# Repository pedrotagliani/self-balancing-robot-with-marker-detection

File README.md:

<h1 align="center">Robot balanceador con detección de marcadores ArUco</h1>

<p>
En este proyecto, se diseñó y construyó un robot balanceador con dos funcionalidades principales. En primer lugar, se implementó un sistema de control remoto mediante una aplicación móvil, que permite mover el robot libremente en cualquier dirección. En segundo lugar, se desarrolló un sistema de equilibrio dinámico que utiliza una cámara para detectar marcadores ArUco y avanzar automáticamente cuando identifica uno en la imagen capturada.

El sistema de control de balance se basó en un controlador PID, ajustado para mantener al robot erguido en todo momento. Para medir el ángulo de inclinación, se utilizó un sensor MPU6050, que combina acelerómetro y giroscopio. Los datos obtenidos por este sensor fueron procesados en un Arduino Nano, que calculaba las señales de control necesarias para los motores. Además, se diseñaron y fabricaron placas PCB personalizadas para integrar los componentes eléctricos del sistema de manera eficiente.

El robot utilizó dos motores paso a paso NEMA 17, seleccionados por su precisión y torque, junto con controladores Pololu A4988 que gestionaron la dirección y velocidad de los motores. Para la comunicación remota, se incorporó un módulo Bluetooth HC-05, que permitió manejar el robot desde una aplicación móvil con una interfaz tipo joystick, facilitada por la biblioteca BalancingWii. Este sistema proporcionó un control intuitivo y responsivo del robot mediante una conexión estable y confiable.

El equilibrio dinámico se logró gracias al controlador PID, que ajustaba de manera constante la velocidad de los motores en función de la inclinación detectada por el sensor. Este algoritmo permitió que el robot se adaptara rápidamente a cambios en el terreno o a variaciones en su carga, manteniéndose estable en diversas condiciones.

En un segundo código, se integraron nuevas funcionalidades para dotar al robot de mayor autonomía mediante el uso de una cámara ESP32-CAM. Este sistema permitió que el robot identificara marcadores ArUco en su entorno y actuara en consecuencia. La comunicación entre el ESP32-CAM y un script en Python, ejecutado en una computadora, se estableció a través de WiFi, utilizando una URL específica para acceder a las imágenes capturadas.

El script en Python procesa estas imágenes en tiempo real, tras realizar la calibración de la cámara mediante tableros ChArUco. Posteriormente, se emplean funciones avanzadas de OpenCV para detectar marcadores ArUco en las imágenes procesadas.

Finalmente, este script se conecta con el robot mediante Bluetooth, permitiendo que el robot recibiera alertas cada vez que se detectaba un marcador en las imágenes. Con esta información, el robot avanzaba de manera autónoma hacia el marcador identificado, logrando un desplazamiento eficiente y preciso hacia el objetivo.
</p>

---

## Integrantes
- Daiana Belén Viscarra Hernández.
- Pedro Tagliani.

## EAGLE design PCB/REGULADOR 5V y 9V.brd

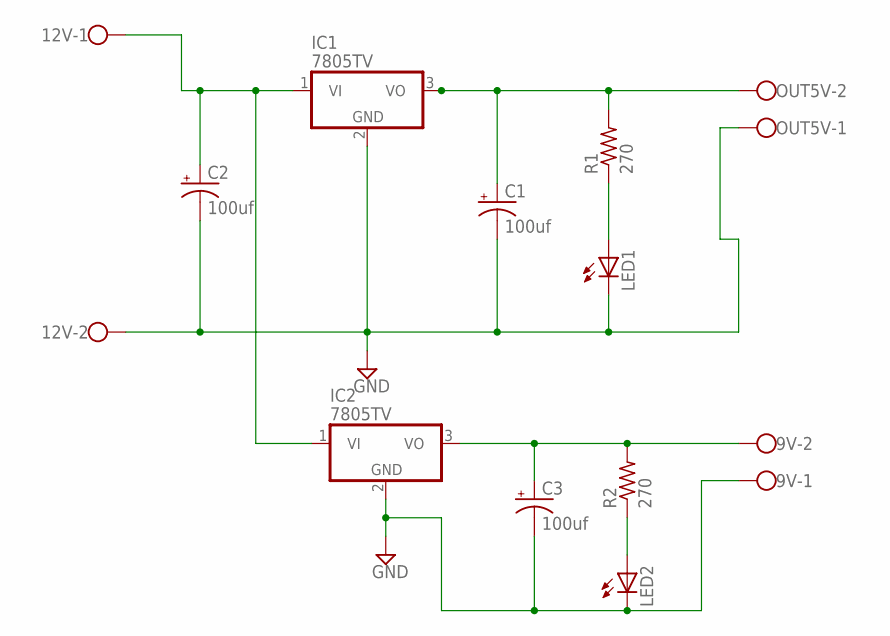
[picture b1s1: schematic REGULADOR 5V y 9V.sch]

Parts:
9V, 12V: W237-102
C1, C2, C3: 100uf; E2,5-5
IC1, IC2: 7805TV; TO220V
LED1, LED2: LED5MM
OUT5V: W237-102
R1, R2: 270; 0204/7

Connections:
GND: 9V.1, 12V.2, C1.-, C2.-, C3.-, IC1.2 (GND), IC2.2 (GND), LED1.K (C), LED2.K (C), OUT5V.1
unnamed: 12V.1, C2.+, IC1.1 (VI), IC2.1 (VI)
unnamed: C1.+, IC1.3 (VO), OUT5V.2, R1.2
unnamed: LED1.A, R1.1
unnamed: 9V.2, C3.+, IC2.3 (VO), R2.2
unnamed: LED2.A, R2.1

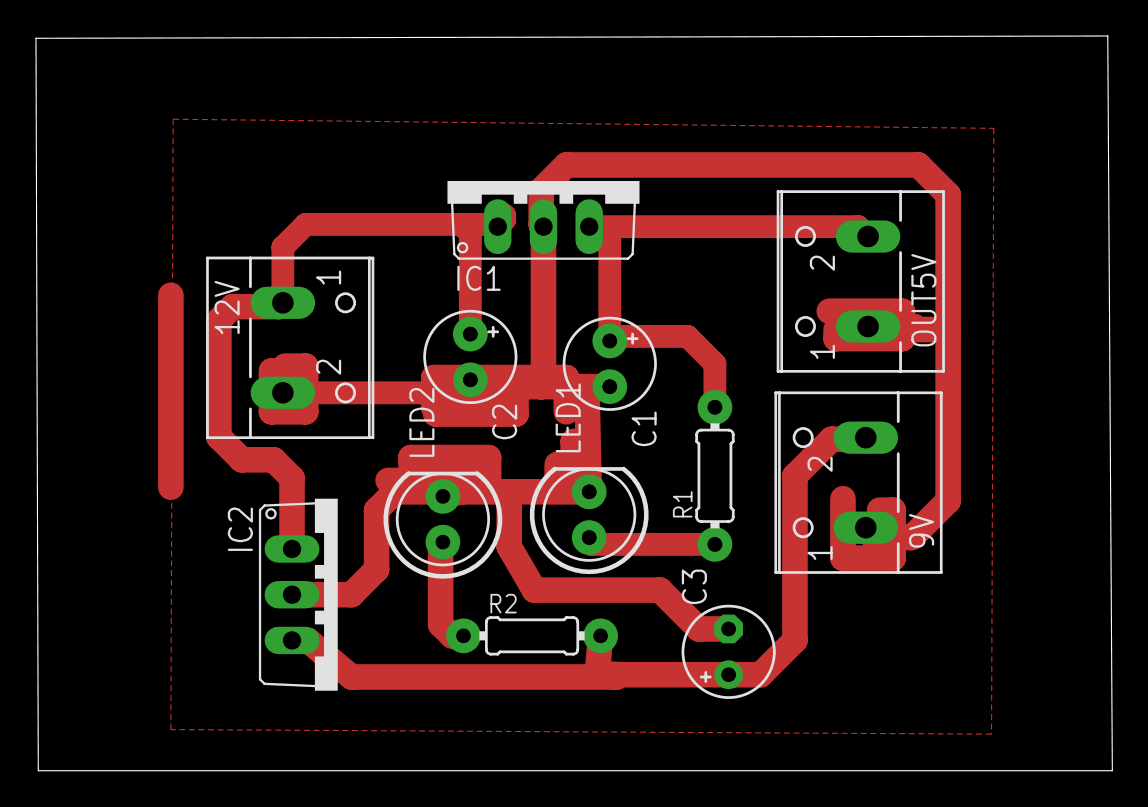
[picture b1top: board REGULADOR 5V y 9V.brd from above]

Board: 2 copper layers, 59.8 x 40.8 mm, 12 parts (0 on the bottom side), 6 nets.

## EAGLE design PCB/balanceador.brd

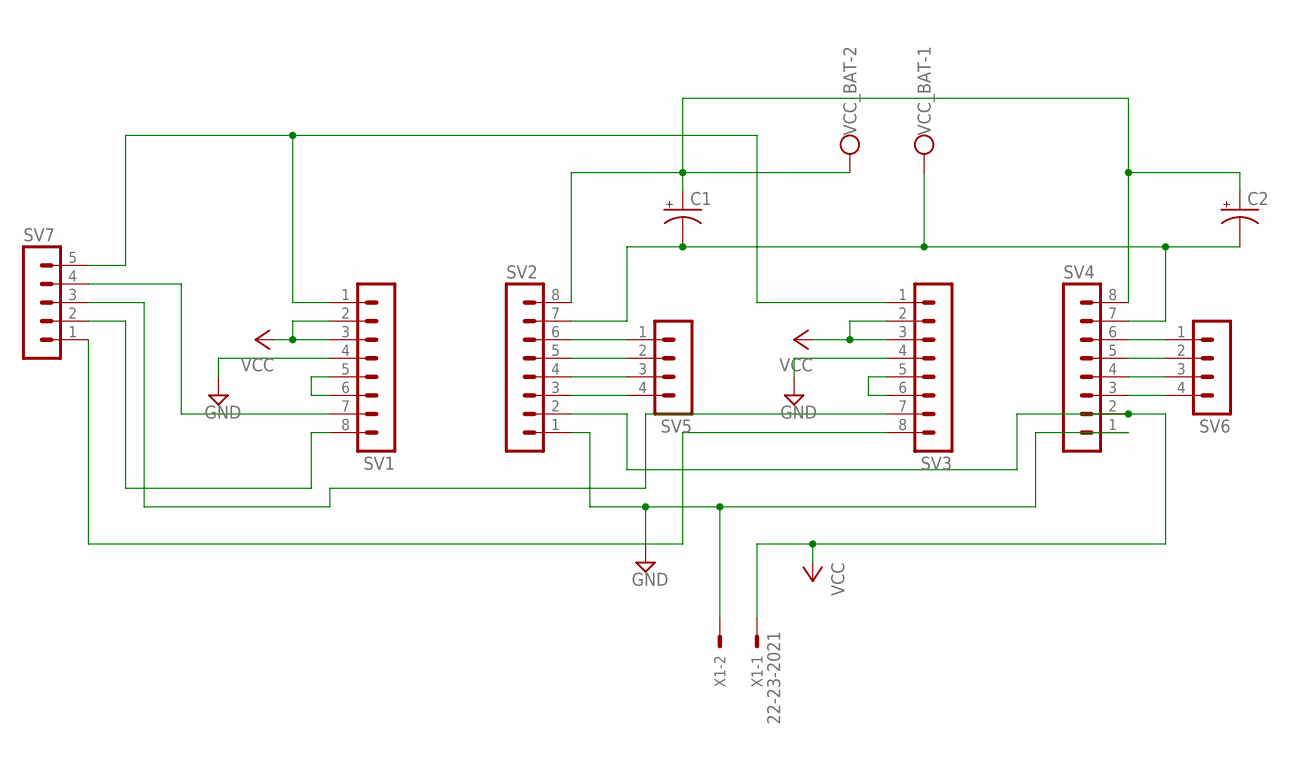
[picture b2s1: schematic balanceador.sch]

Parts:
C1, C2: CPOL-USE2.5-6; E2,5-6
SV1, SV2, SV3, SV4: MA08-1
SV5, SV6: MA04-1
SV7: MA05-1
VCC_BAT: W237-102
X1: 22-23-2021

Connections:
GND: SV1.4, SV2.1, SV3.4, SV4.1, X1.2
unnamed: SV2.6, SV5.1
unnamed: SV2.5, SV5.2
unnamed: SV2.4, SV5.3
unnamed: SV2.3, SV5.4
unnamed: SV4.6, SV6.1
unnamed: SV4.5, SV6.2
unnamed: SV4.4, SV6.3
unnamed: SV4.3, SV6.4
unnamed: SV3.5, SV3.6
unnamed: C1.+, C2.+, SV2.8, SV4.8, VCC_BAT.2
unnamed: SV1.5, SV1.6
unnamed: C1.-, C2.-, SV2.7, SV4.7, VCC_BAT.1
unnamed: SV1.8, SV7.2
unnamed: SV1.1, SV3.1, SV7.5
unnamed: SV3.8, SV7.1
unnamed: SV1.7, SV7.4
unnamed: SV3.7, SV7.3
VCC: SV1.2, SV1.3, SV2.2, SV3.2, SV3.3, SV4.2, X1.1

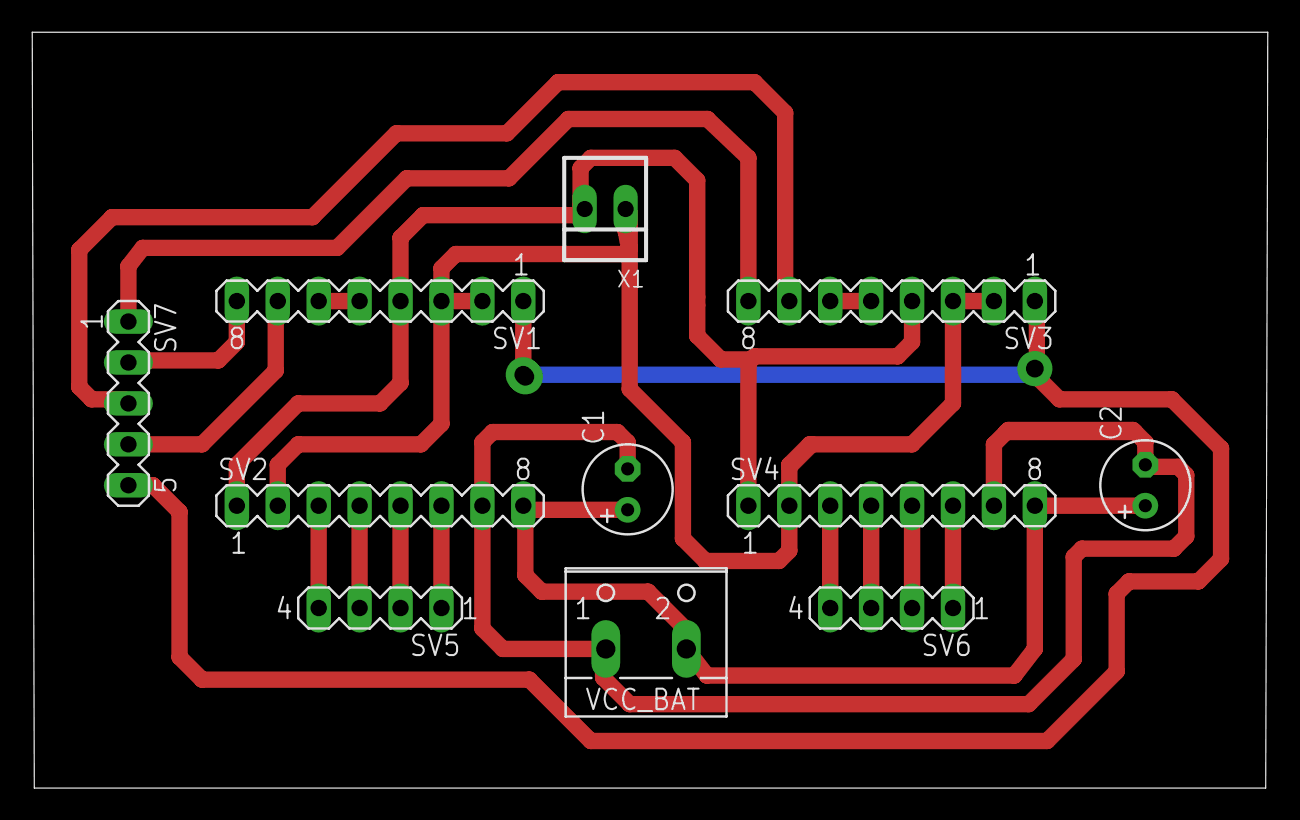
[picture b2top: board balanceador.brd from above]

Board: 2 copper layers, 76.7 x 46.9 mm, 11 parts (0 on the bottom side), 19 nets.

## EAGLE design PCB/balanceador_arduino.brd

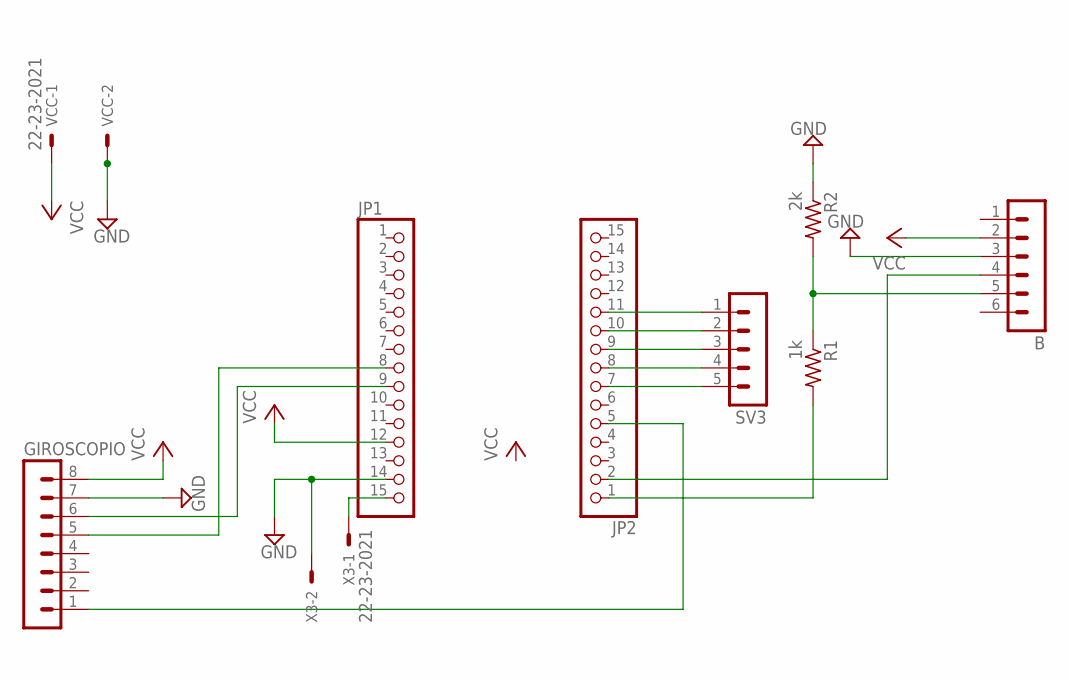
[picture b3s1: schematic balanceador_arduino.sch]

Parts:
B: MA06-1
GIROSCOPIO: MA08-1
JP1, JP2: PINHD-1X15; 1X15
R1: 1k; 0204/7
R2: 2k; 0204/7
SV3: MA05-1
VCC: 22-23-2021
X3: 22-23-2021

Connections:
D4: JP2.7, SV3.5
GND: B.3, GIROSCOPIO.7, JP1.14, R2.1, VCC.2, X3.2
unnamed: B.5, R1.1, R2.2
unnamed: GIROSCOPIO.6, JP1.9
unnamed: GIROSCOPIO.5, JP1.8
unnamed: JP2.1, R1.2
unnamed: B.4, JP2.2
unnamed: GIROSCOPIO.1, JP2.5
unnamed: JP2.8, SV3.4
unnamed: JP2.9, SV3.3
unnamed: JP2.10, SV3.2
unnamed: JP2.11, SV3.1
unnamed: JP1.15, X3.1
VCC: B.2, GIROSCOPIO.8, JP1.12, VCC.1

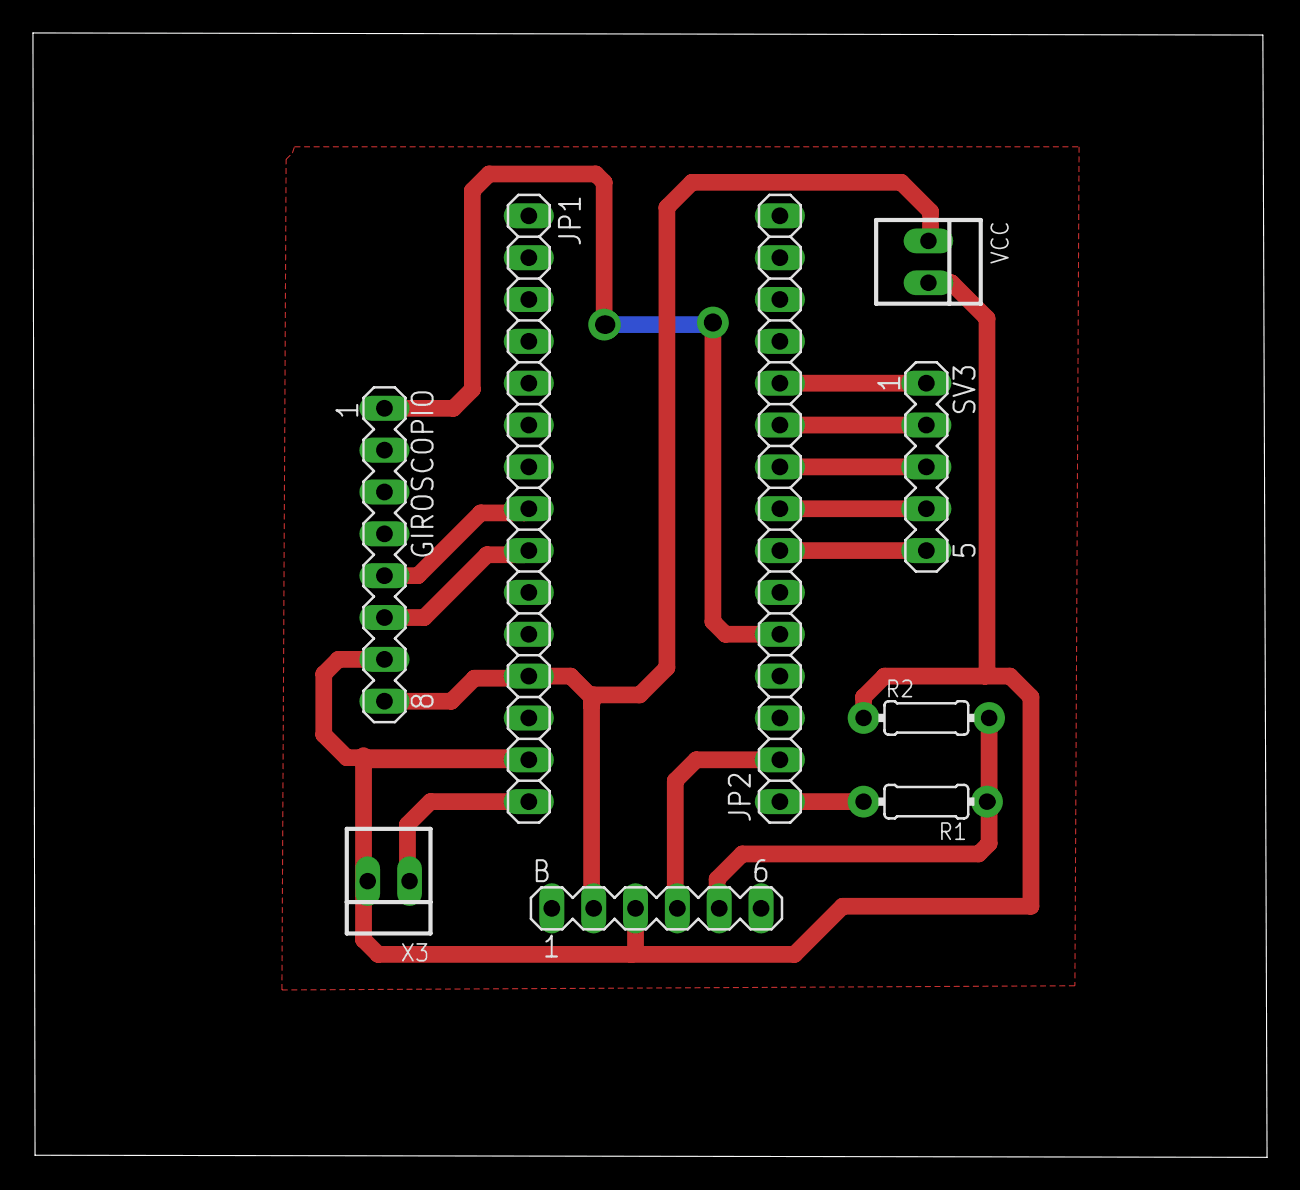
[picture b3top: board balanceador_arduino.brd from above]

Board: 2 copper layers, 74.9 x 68.2 mm, 9 parts (0 on the bottom side), 14 nets.

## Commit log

2024-11-28 Test files
2024-12-03 First attempt
2024-12-04 Stepper motors control is now performed with registers
2024-12-09 Made corrections
2024-12-19 Latest update
    BalancingWii module added and manual control through ArUco marker (ID 5).
2024-12-19 BalancingWii fixed
2024-12-19 Upload PCB + Schematics
2024-12-19 Upload images
2024-12-19 Upload image
